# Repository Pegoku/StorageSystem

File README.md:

# Smart Storage System

## Overview
This is a versatile and customizable Storage System. It has the ability to combine multiple Storage Systems via the use of ESP32 (a cheap microcontroller) as controllers for the neopixels (indicators). It has a simple but useful WebUI and an API. The storage bins are compatible with Gridfinity 1x4 bins.

## Features
- [x] **Gridfinity Compatible**: Easily integrates with the Gridfinity storage system for modular storage.
- [x] **Parametric Design**: Easily customizable bins.
- [x] **ESP32 Controlled**: Scalable system using ESP32 as wireless controllers.
- [x] **Neopixels**: Dynamic lighting indicators.
- [x] **Web UI to Manage Storage**: User-friendly web interface for managing the items.
- [x] **API**: Simple to use API.
- [x] **Node PCB**: Simple ESP32-Wroom based PCB with the necessary connectors.

## Media
<details>
    <summary>Main Website</summary>

</details>

<details>
    <summary>Add Item Menu</summary>

</details>

<details>
    <summary>Video</summary>

</details>

## API Endpoints

### List Storage Items
- **Endpoint**: `/api/list`
- **Method**: `GET`
- **Description**: Retrieves a list of all storage items. Supports optional query parameters for filtering by category, node, and position.
- **Query Parameters**:
  - `category` (optional): Filter items by category.
  - `node` (optional): Filter items by node.
  - `position` (optional): Filter items by position.
  - `id` (optional): Filter items by ID:
### Locate Item by ID (GET)
- **Endpoint**: `/api/locateget`
- **Method**: `GET`
- **Description**: Locates an item by its ID and sends a request to the corresponding node to locate the item.
- **Query Parameters**:
  - `id` (required): The ID of the item to locate.

### List Nodes
- **Endpoint**: `/api/nodes`
- **Method**: `GET`
- **Description**:  Retrieves a list of all nodes. Supports optional query parameter for filtering by ID.
- **Query Parameters**:
    - `id` (optional): Filter nodes by ID.

### Add Storage Item
- **Endpoint**: `/api/additem`
- **Method**: `POST`
- **Description**: Adds a new storage item to the database.
- **Request Body** (JSON):
  ```json
  {
    "name": "string",
    "description": "string",
    "category": "string",
    "quantity": "integer",
    "node": "integer",
    "position": "integer",
    "url": "string",
    "slots": "array"

  }
  ```

### Add Node
- **Endpoint**: `/api/addnode`
- **Method**: `POST`
- **Description**:  Adds a new node to the database or updates an existing node if the ID already exists.
- **Request Body** (JSON):
  ```json
    {
      "id": "integer",
      "ip": "string",
      "positions": "integer"
    }
  ```

### Delete Storage Item
- **Endpoint**: `/api/delete`
- **Method**: `POST`
- **Description**:   Deletes a storage item by its ID.
- **Request Body** (JSON):
  ```json
    {
      "id": "integer"
    }
  ```

### Edit Storage Item
- **Endpoint**: `/api/edit`
- **Method**: `POST`
- **Description**:  Edits an existing storage item by its ID.
- **Request Body** (JSON):
  ```json
    {
    "id": "integer",
    "name": "string",
    "description": "string",
    "category": "string",
    "quantity": "integer",
    "node": "integer",
    "position": "integer",
    "url": "string",
    "slots": "array"
    }   
  ```

### Move Storage Item
- **Endpoint**: `/api/move`
- **Method**: `POST`
- **Description**:  Moves a storage item to a different node and position.
- **Request Body** (JSON):
  ```json
    {
    "id": "integer",
    "node": "integer",
    "position": "integer"
    }
  ```

### Locate Item by ID (POST)
- **Endpoint**: `/api/locate`
- **Method**: `POST`
- **Description**:  Locates an item by its ID and sends a request to the corresponding node to locate the item.
- **Request Body** (JSON):
  ```json
    {
    "id": "integer"
    }
  ```

## Getting Started

### Prerequisites
- [PlatformIO](https://platformio.org) installed on your development environment.
- ESP32 DevBoard or [Node PCB](https://github.com/Pegoku/StorageSystem/tree/master/PCB/NodePCB) .
- Neopixels (WS2812B) or [Indicator PCB](https://github.com/Pegoku/StorageSystem/tree/master/PCB/Indicators).
- Some wire.
- Edit Code/App/static/script.js `server` variable
- Edit Code/Node/include/.env with the correct settings

### Docker (API + Website)
1. Clone the repository:
    ```sh
    git clone https://github.com/Pegoku/StorageSystem.git
    cd StorageSystem
    ```
2. Build and run the Docker containers:
  ```sh
  docker compose up -d --build
  ```

### API 
1. Clone the repository:
    ```sh
    git clone https://github.com/Pegoku/StorageSystem.git
    cd StorageSystem/Code/Server
    ```
2. Create a Python virtual environment and install the requirements:
    ```sh
    python3 -m venv .venv
    source .venv/bin/activate
    pip install -r requirements.txt
    ```
3. Run the main Python file:
    ```sh
    python3 main.py
    ```

### API (Docker)
1. Clone the repository:
  ```sh
  git clone https://github.com/Pegoku/StorageSystem.git
  cd StorageSystem
  ```
2. Build and run the Docker container:
  ```sh
  docker buildx build -t storagesystem:server -f server.Dockerfile .
  docker run -p 5505:5505 -v ./database.db:/app/database.db storagesystem:server
  ```
3. The API should now be running and accessible at `http://localhost:5505`.

### ESP32
1. Clone the repository:
    ```sh
    git clone https://github.com/Pegoku/StorageSystem.git
    cd StorageSystem
    ```
2. Install the required libraries and dependencies:
    ```sh
    platformio run
    ```
3. Connect your ESP32 to your computer.
4. Edit the `include/.env.template` file and rename it to `include/.env`.
5. Upload the firmware to the ESP32:
    ```sh
    platformio run --target upload
    ```
6. Open the serial monitor to check if the installation was successful:
    ```sh
    platformio device monitor
    ```

### Website
1. Clone the repository:
    ```sh
    git clone https://github.com/Pegoku/StorageSystem.git
    cd StorageSystem/Code/App
    ```
2. Create a Python virtual environment and install the requirements:
    ```sh
    python3 -m venv .venv
    source .venv/bin/activate
    pip install -r requirements.txt
    ```
3. Run the main Python file:
    ```sh
    python3 main.py
    ```

### Website (Docker)
1. Clone the repository:
  ```sh
  git clone https://github.com/Pegoku/StorageSystem.git
  cd StorageSystem
  ```
2. Build and run the Docker container:
  ```sh
  docker buildx build -t storagesystem:app -f app.Dockerfile .
  docker run -p 5506:5506 storagesystem:app
  ```
3. The website should now be running and accessible at `http://localhost:5506`.

## Contributing
Contributions are welcome! Please fork the repository and submit a pull request with your changes.

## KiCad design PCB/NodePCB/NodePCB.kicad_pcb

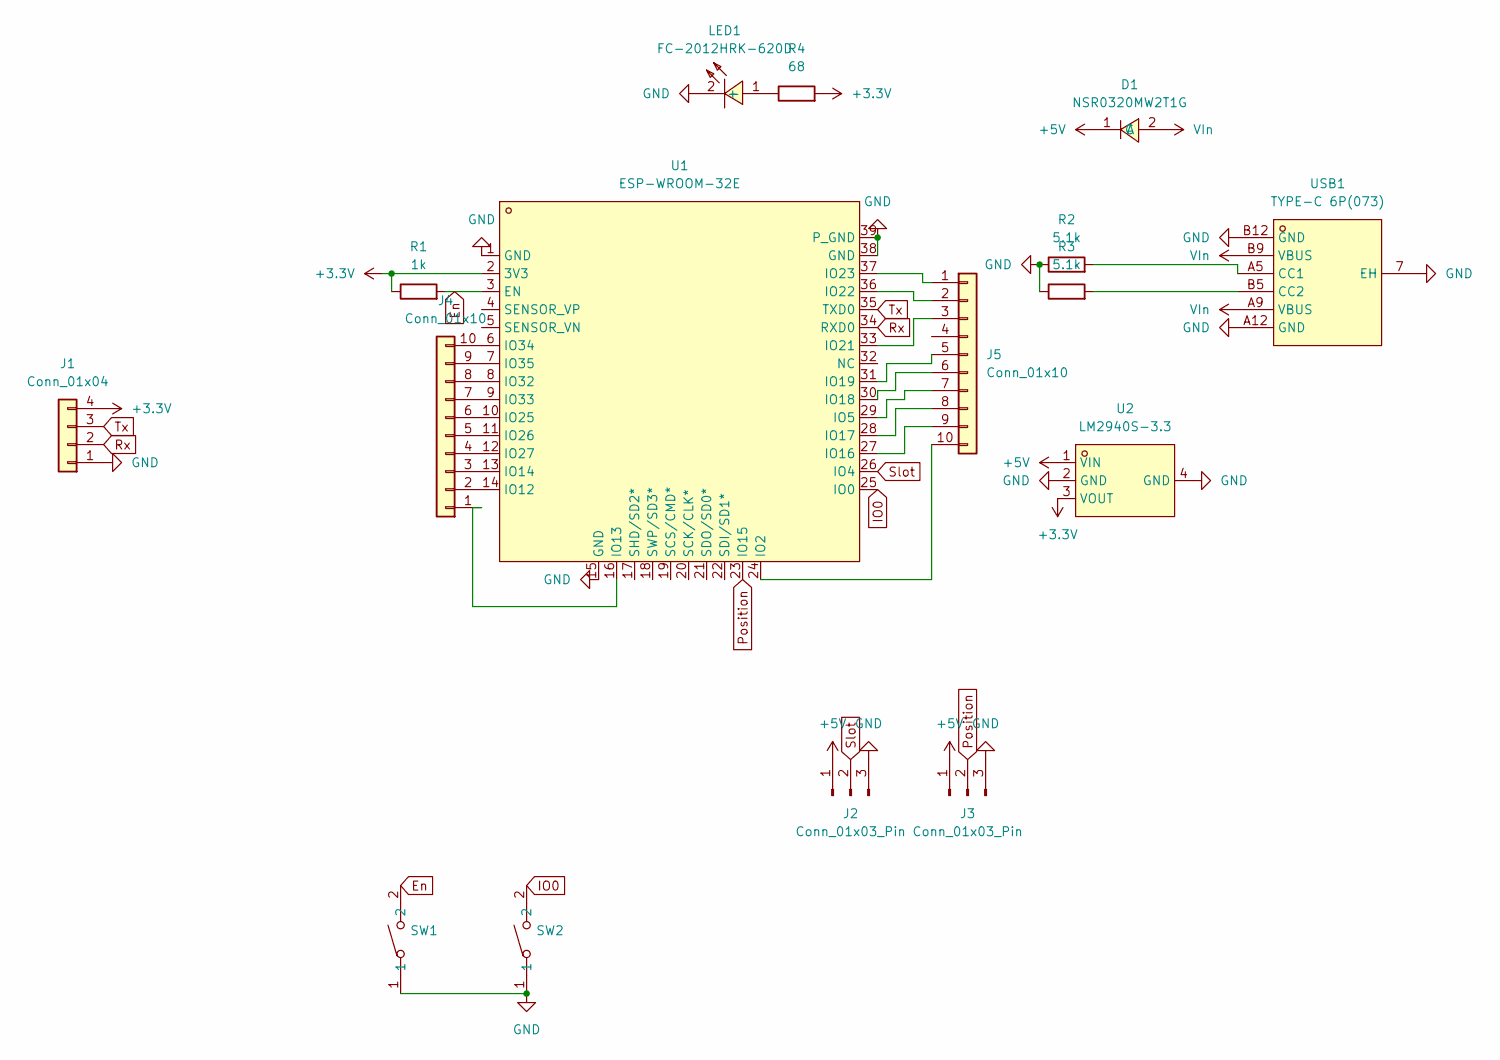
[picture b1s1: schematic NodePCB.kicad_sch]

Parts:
D1: NSR0320MW2T1G; SOD-323_L1.8-W1.3-LS2.5-RD; LCSC Part C48192
J1: Conn_01x04; PinHeader_1x04_P2.54mm_Horizontal
J2, J3: Conn_01x03_Pin; PinHeader_1x03_P2.54mm_Horizontal
J4, J5: Conn_01x10; PinHeader_1x10_P2.54mm_Vertical
LED1: FC-2012HRK-620D; LED0805-R-RD; LCSC Part C84256
R1: 1k; R_0603_1608Metric
R2, R3: 5.1k; R_0603_1608Metric
R4: 68; R_0603_1608Metric
SW1, SW2: TS-1088-AR02016; SW-SMD_L3.9-W3.0-P4.45; LCSC Part C720477
U1: ESP-WROOM-32E; COMM-SMD_ESP-WROOM-32D; LCSC Part C19949066
U2: LM2940S-3.3; SOT-223-3_L6.5-W3.4-P2.30-LS7.0-BR; LCSC Part C596335
USB1: TYPE-C 6P(073); TYPE-C-SMD_TYPE-C-6P_5; LCSC Part C668623

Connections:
+3.3V: J1.4, R1.1, R4.2, U1.2 (3V3), U2.3 (VOUT)
+5V: D1.1 (C), J2.1, J3.1, U2.1 (VIN)
En: R1.2, SW1.2, U1.3 (EN)
GND: J1.1, J2.3, J3.3, LED1.2 (-), R2.1, R3.1, SW1.1, SW2.1, U1.1 (GND), U1.15 (GND), U1.38 (GND), U1.39 (P_GND), U2.2 (GND), U2.4 (GND), USB1.7 (EH), USB1.A12 (GND), USB1.B12 (GND)
IO0: SW2.2, U1.25 (IO0)
unnamed: J4.1, U1.16 (IO13)
unnamed: J4.2, U1.14 (IO12)
unnamed: J4.3, U1.13 (IO14)
unnamed: J4.4, U1.12 (IO27)
unnamed: J4.5, U1.11 (IO26)
unnamed: J4.6, U1.10 (IO25)
unnamed: J4.7, U1.9 (IO33)
unnamed: J4.8, U1.8 (IO32)
unnamed: J4.9, U1.7 (IO35)
unnamed: J4.10, U1.6 (IO34)
unnamed: J5.1, U1.37 (IO23)
unnamed: J5.2, U1.36 (IO22)
unnamed: J5.3, U1.33 (IO21)
unnamed: J5.5, U1.31 (IO19)
unnamed: J5.6, U1.30 (IO18)
unnamed: J5.7, U1.29 (IO5)
unnamed: J5.8, U1.28 (IO17)
unnamed: J5.9, U1.27 (IO16)
unnamed: J5.10, U1.24 (IO2)
unnamed: LED1.1 (+), R4.1
unnamed: R2.2, USB1.A5 (CC1)
unnamed: R3.2, USB1.B5 (CC2)
Position: J3.2, U1.23 (IO15)
Rx: J1.2, U1.34 (RXD0)
Slot: J2.2, U1.26 (IO4)
Tx: J1.3, U1.35 (TXD0)
VIn: D1.2 (A), USB1.A9 (VBUS), USB1.B9 (VBUS)

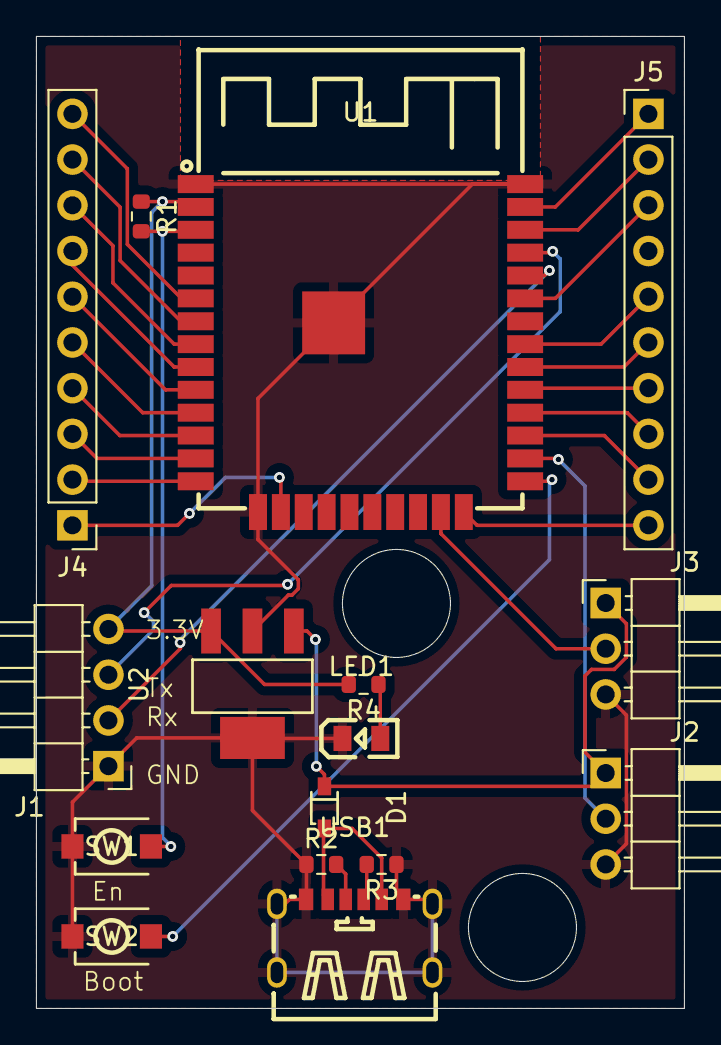
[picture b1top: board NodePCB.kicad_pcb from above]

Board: 2 copper layers, 36.0 x 54.0 mm, 16 parts (0 on the bottom side), 32 nets.

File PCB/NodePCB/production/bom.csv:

Designator,Footprint,Quantity,Value,LCSC Part #
D1,SOD-323_L1.8-W1.3-LS2.5-RD,1,NSR0320MW2T1G,C48192
J1,PinHeader_1x04_P2.54mm_Horizontal,1,Conn_01x04,
"J2, J3",PinHeader_1x03_P2.54mm_Horizontal,2,Conn_01x03_Pin,
"J4, J5",PinHeader_1x10_P2.54mm_Vertical,2,Conn_01x10,
LED1,LED0805-R-RD,1,FC-2012HRK-620D,C84256
R1,0603,1,1k,
"R2, R3",0603,2,5.1k,
R4,0603,1,68,
"SW1, SW2",SW-SMD_L3.9-W3.0-P4.45,2,TS-1088-AR02016,C720477
U1,COMM-SMD_ESP-WROOM-32D,1,ESP-WROOM-32E,C19949066
U2,SOT-223-3_L6.5-W3.4-P2.30-LS7.0-BR,1,LM2940S-3.3,C596335
USB1,TYPE-C-SMD_TYPE-C-6P_5,1,TYPE-C 6P(073),C668623

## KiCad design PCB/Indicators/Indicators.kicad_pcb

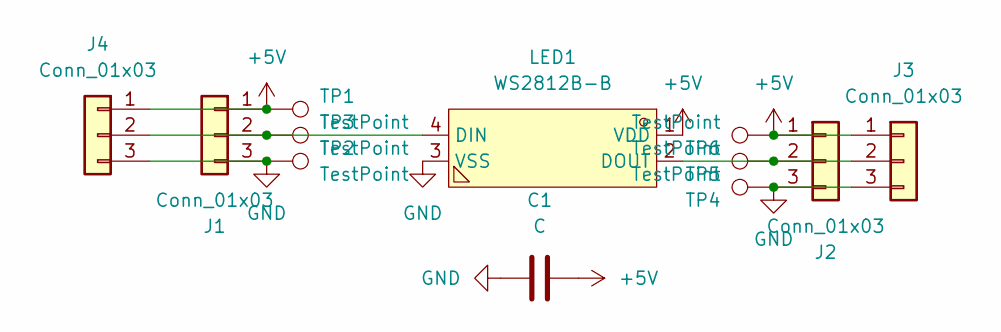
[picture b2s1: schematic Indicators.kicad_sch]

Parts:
C1: C; C_0603_1608Metric; LCSC C2844328
J1, J2: Conn_01x03; PinHeader_1x03_P2.54mm_Horizontal
J3, J4: Conn_01x03; PinSocket_1x03_P2.54mm_Horizontal
LED1: WS2812B-B; LED-SMD_4P-L5.0-W5.0-BL_TC5050RGB; LCSC Part C114586
TP1, TP2, TP3, TP4, TP5, TP6: TestPoint; TestPoint_Pad_D1.5mm

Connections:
+5V: C1.2, J1.1, J2.1, J3.1, J4.1, LED1.1 (VDD), TP1.1, TP6.1
GND: C1.1, J1.3, J2.3, J3.3, J4.3, LED1.3 (VSS), TP2.1, TP4.1
unnamed: J1.2, J4.2, LED1.4 (DIN), TP3.1
unnamed: J2.2, J3.2, LED1.2 (DOUT), TP5.1

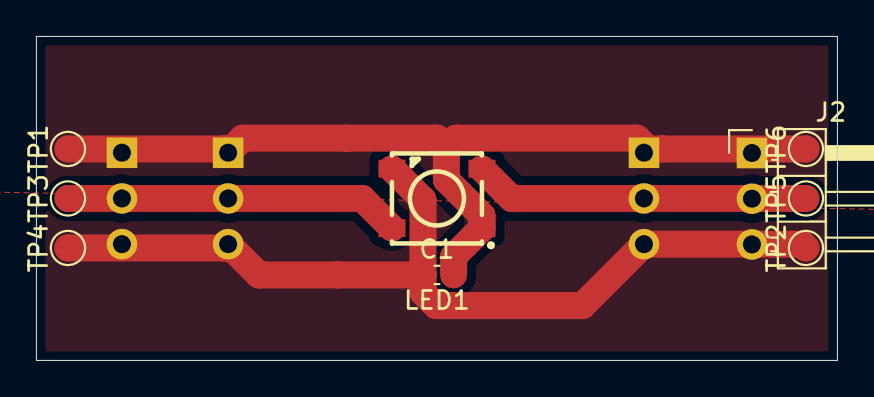
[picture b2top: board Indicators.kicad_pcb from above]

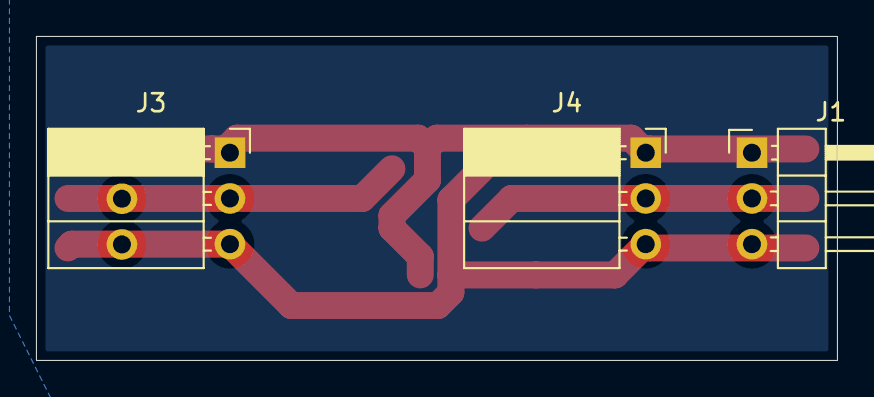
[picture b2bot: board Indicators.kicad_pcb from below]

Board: 2 copper layers, 44.5 x 18.0 mm, 12 parts (3 on the bottom side), 4 nets.

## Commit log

2024-11-04 working filtering system
2024-11-09 working add and list
2024-11-10 working locate
2024-11-10 working API
2024-11-17 working link and update ip from node
2024-11-18 Seems to be working
2024-11-19 Added Search for Name and category
2024-11-19 Add readme
2024-12-09 finish
2024-12-11 fix readme
2024-12-14 add edit button
2024-12-14 better link filter
2024-12-17 fix bugs
2024-12-18 add docker support
2025-01-17 modify models + finish
2025-01-17 add compose
2025-01-17 edit default port for compatibility
2025-01-26 Added Node PCB
2025-02-27 added /api call
